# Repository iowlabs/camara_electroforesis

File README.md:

# Cámara electroforésis

Este proyecto tiene como objetivo el diseño de una cámara de electroforesis de bajo costo y fácil acceso, ideal para entornos educativos, laboratorios escolares,  iniciativas de ciencia ciudadana, equipamientos de bajo costo o laboratorios portátiles. El sistema completo incluye tanto la cámara donde se realiza la separación de moléculas como una fuente de poder casera que permite aplicar el voltaje necesario para el experimento.

El diseño y la implementación de este proyecto están fuertemente inspirados en la documentación proporcionada por IORodeo, quienes han compartido detalladamente cómo construir sistemas de electroforesis caseros. En particular, se han seguido y adaptado los siguientes recursos:

- [Cámara de electroforesis - Instructables](https://www.instructables.com/Gel-electrophoresis-system-mini/)
- [Fuente de poder - Instructables](https://www.instructables.com/Gel-electrophoresis-power-supply/)

Este repositorio prone un nuevo diseño orientado a consolidar y empaquetar el proceso de fabricación de los componentes por medio de nuevos diseños basados principalmente en impresión 3D. De este modo se consolida la información, archivos de diseño, materiales necesarios y las mejoras propuestas por iow Labs con la intención de facilitar la replicabilidad y su uso por parte de otras personas o instituciones interesadas en el uso de tecnologías abiertas en la ciencia.

---
# Licencias
Todos los archivos involucrados en este proyecto se encuentran bajo licencias abiertas, para su replicabilidad y comercialización.

| Tipo de archivo | Licencia |
| ---             |  -----   |
| Electronica 	  |  CERN-OHL-S-2.0 |
| Software y firmware |  GPL-3.0-or-later|
| Diseños 3D |  CERN-OHL-S-2.0 |
| Archivos de documentación | CC-BY-SA-4.0 |

---

# Cámara

En este diseño se propone un modelo de cámara impreso totalmente, como una pieza continua. De este modo, se facilita el proceso de fabricación evitando trabajar con acrílico y las complicaciones que esto implica.

## Materiales

Los tanques para la electróforesis habitualmente se fabrican con acrílico, sin embargo el proceso de cortado y pegado suele ser dificil de gestionar ya que requiere habilidades manuales princilamnte debido a que involucra la manipulación de cloroformo.

Para evitar esto, se implementó una alternativa basada en impresión 3D. Para replicar las características del acrílico se evaluaron diferentes materialidades y metodologías. Finalmente, se optó por imprimir el cuerpo del tanque en PETG para garantizar el buen desempeño en altas temperaturas y para garantizar la impermeabilidad, se optó por aplicarle una capa de resina epoxyca al interior. La tapa se realiza en un solo corte acrílico, para garantizar la transparencia.   

| Pieza 	| Material | Archivo |
| --------- | -------- | ------- |
| Tanque   	|  PETG    | [tanque_V2.stl](https://github.com/iowlabs/camara_electroforesis/blob/main/3d%20models/tank_v2.stl) |
| Tapa		| Acrílico | [tapa_V2.stl](https://github.com/iowlabs/camara_electroforesis/blob/main/3d%20models/tapa_v2.stl) |

### Instrucciones de fabricación

## Lista de materiales

| N    | Componente 	| Cantidad | Comentario |
|------|----------------|----------|------------|
| 1    | Tanque         |  1       |            |
| 2    | Tapa           |  1       |            |
| 3    | Conectores banana     |  2   | Tipo macho |
| 4    | Electrodos de pt |  2   | arpox 20cm de cable de 0.01'' de platino           |

## Instrucciones de armado

---

# Fuente de poder

Para implementar la fuente se diseñó una PCB que integre los componentes considerando en su mayoría componentes SMD. Esta PCB consiste en la implementación de un conversor DC/DC del tipo chopper bust. Este diseño se basa en el integrado MAX117 y la topología utilizada se encuentra detallada en los siguientes documentos 3,4,5
Esta topología es utilizada ampliamente por diferentes proyectos como el Open Drop o la misma fuente de electroforesis de IORodeo. Adicionalmente se consideró agregar un microcontrolador de la familia ESP32S3 para agregar nuevas funcionalidades al diseño y poder considerar en una implementación futura las capacidades de conectividad para montar  una red Lab on a Web que permita controlar todo el laboratorio de forma centralizada y remota.

El esquemático completo se entrega en la siguiente imagen.

A continuación se entregan imágenes de las visualizaciones 3D del render de la PCB

La PCB considera la integración de una interfaz de usuario implementada por medio de un rotary switch y una pantalla OLED con el objetivo de visualizar el valor actual de voltaje de salida.

Para integrar todos los componentes de forma segura se ha diseñado un casing 3D impreso en PLA.

### Archivos de fabricación
Los archivos de fabricación de la PCB se encuentran disponibles en formato ZIP en el directorio de [archivos de salida](https://github.com/iowlabs/camara_electroforesis/tree/main/electronics/fuente_regulable/output_files) listos para ser enviados a fabricación.

Para el casing, los archivos se encuentran en la carpeta de modelos 3D.

| Pieza 	| Material | Archivo |
| --------- | -------- | ------- |
| Tapa superior   	|  PLA   | [fure_tapa.step](https://github.com/iowlabs/camara_electroforesis/blob/main/3d%20models/fure_tapa.step) |
| Cara frontal		| PLA | [fure_cara.step](https://github.com/iowlabs/camara_electroforesis/blob/main/3d%20models/fure_cara.step) |
|  Base		| PLA | [fure_base.step](https://github.com/iowlabs/camara_electroforesis/blob/main/3d%20models/fure_base.step) |

### BOM de PCB
La lista de los componentes se encuentra disponible en el archivo BOM  [fuente_regulable_bom.csv](https://github.com/iowlabs/camara_electroforesis/blob/main/electronics/fuente_regulable/output_files/fuente_regulable_bom.csv), como referencia se consideran de LCSC.

### Lista de materiales para la fuente regulable.

| N    | Componente 	| Cantidad | Comentario |
|------|----------------|----------|------------|
| 1    | FuRe PCB         |  1       | PCB by iow Labs |
| 2    | Conectores banana|  2       |  Tipo hembra  |
| 3    | Cables banana     |  2   | Tipo macho - hembra |
| 4    | Switch on/off |  1   |  |
| 5    | Rotary encoder switch |  1   |  |
| 6    | Jack DC |  1   |  |
| 7    | Pantalla OLED |  1   |  |
| 8    | case - superior |  1   | Pieza impresa |
| 9    | case - frontal |  1   | Pieza impresa |
| 10   | case - base |  1   | Pieza impresa |
| 11   | Fuente de 12V |  1   | Al menos 1A (12W) |
| 12   | Tornillos M3 |  6   | Al menos 12mm |
| 13   | Tuercas M3 |  4   |   |
| 14   | Cable AWG 20 |  -   | Para conexiones internas   |
| 15   | Cable AWG 26 - 4 wires |  1   | Cable de la pantalla OLED   |
| 16   | Cable AWG 26 - 5 wires |  1   | Cable del rotary encoder   |

### Firmware

El firmware se puede encontrar en el directorio [firmware](https://github.com/iowlabs/camara_electroforesis/tree/main/firmware). Esta escrito en el framwork de arduino. Para cargarlo correctamente es necesario configurar en el IDE de arduino la placa ESP32-S3. Para esto se puede usar el modelo ESP32-S3-DEV-Kit.

El código subido implementa una interfaz sencilla entre el rotary encoder y el voltaje de salida que se configura en el módulo MAX117 por medio de un potenciomentro digital configurado por SPI.

Todas las bibliotecas utilizadas se encuentran dentro del repositorio oficial de arduino.

## Instrucciones de ensamblado

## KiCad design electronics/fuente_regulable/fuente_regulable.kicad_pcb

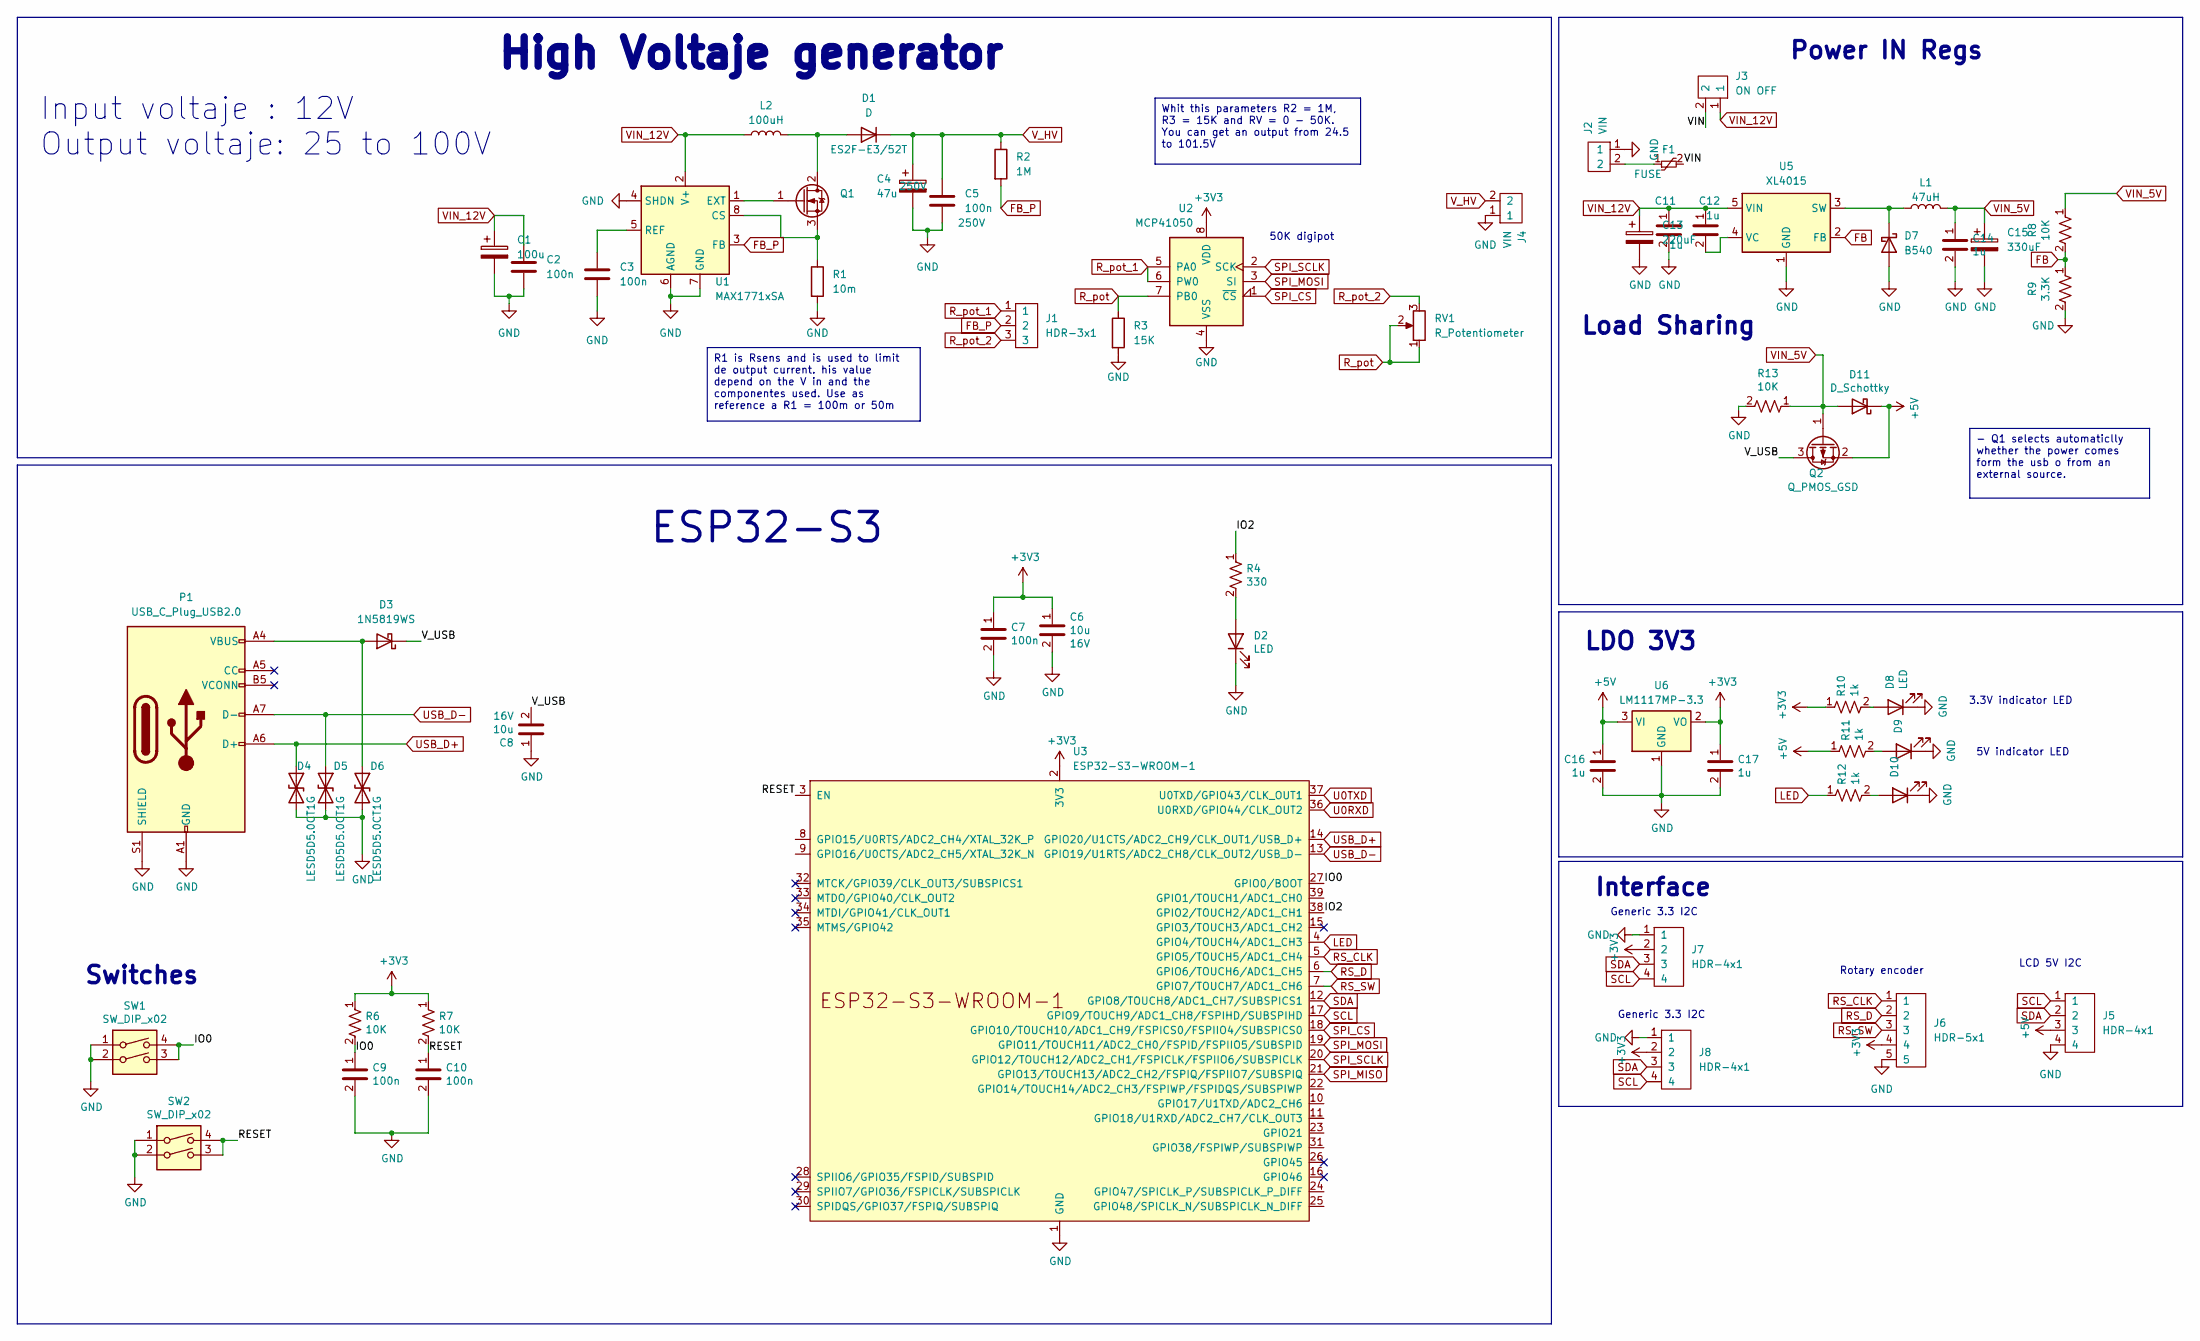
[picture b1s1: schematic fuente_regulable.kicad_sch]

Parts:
C1: 100u; CP_Elec_8x10
C2, C3: 100n; C_0603_1608Metric
C4: 47u; CP_Radial_D13.0mm_P5.00mm
C5: 100n; C_1812_4532Metric
C6, C8: 10u; C_0805_2012Metric; Voltage rated 16V
C7, C9, C10: 100n; C_0603_1608Metric; Voltage rated 16V
C11, C12, C14, C16, C17: 1u; C_0805_2012Metric; Voltage rated 16V
C13: 220uF; CP_Elec_8x10.5; Voltage 50V
C15: 330uF; CP_Elec_8x10.5; Voltage 25V
D1: D; D_SMB
D2, D8, D9, D10: LED; LED_0603_1608Metric
D3: 1N5819WS; D_SOD-323
D4, D5, D6: LESD5D5.0CT1G; D_SOD-523
D7: B540; D_SMB_Handsoldering
D11: D_Schottky; D_SMA
F1: FUSE; Fuse_1206_3216Metric
J1: HDR-3x1; PinHeader_1x03_P2.54mm_Vertical
J2, J4: VIN; Tb-2x1-5p-TH-V
J3: ON OFF; PinHeader_1x02_P2.54mm_Vertical
J5, J7, J8: HDR-4x1; JST_XH_B4B-XH-A_1x04_P2.50mm_Vertical
J6: HDR-5x1; JST_XH_B5B-XH-A_1x05_P2.50mm_Vertical
L1: 47uH; L_12x12mm_H8mm
L2: 100uH; L_12x12mm_H6mm
P1: USB_C_Plug_USB2.0; USB_C_Receptacle_GCT_USB4105-xx-A_16P_TopMnt_Horizontal
Q1: Q_NMOS_Depletion_GDS; TO-220-3_Vertical
Q2: Q_PMOS_GSD; SOT-23
R1: 10m; R_0805_2012Metric
R2: 1M; R_2512_6332Metric
R3: 15K; R_2512_6332Metric
R4: 330; R_0603_1608Metric
R6, R7, R8, R13: 10K; R_0603_1608Metric
R9: 3.3K; R_0603_1608Metric
R10, R11, R12: 1k; R_0603_1608Metric
RV1: R_Potentiometer; PDB18 - Rotary Potentiometer
SW1, SW2: SW_DIP_x02; SMD_SWITCH
U1: MAX1771xSA; SO-8_3.9x4.9mm_P1.27mm
U2: MCP41050; SOIC-8_3.9x4.9mm_P1.27mm
U3: ESP32-S3-WROOM-1
U5: XL4015; TO-263-5_TabPin3
U6: LM1117MP-3.3; SOT-223-3_TabPin2

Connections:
+3V3: C6.1, C7.1, C17.1, J6.4, J7.2, J8.2, R6.1, R7.1, R10.1, U2.8 (VDD), U3.2 (3V3), U6.2 (VO)
+5V: C16.1, D11.1 (K), J5.3, Q2.2 (S), R11.1, U6.3 (VI)
/IO0: C9.1, R6.2, SW1.3, SW1.4, U3.27 (GPIO0/BOOT)
/IO2: R4.1, U3.38 (GPIO2/TOUCH2/ADC1_CH1)
/RESET: C10.1, R7.2, SW2.3, SW2.4, U3.3 (EN)
/VIN: F1.2, J3.2
/V_USB: C8.2, D3.1 (K), Q2.3 (D)
FB: R8.2, R9.1, U5.2 (FB)
FB_P: J1.2, R2.2, U1.3 (FB)
GND: C1.2, C2.2, C3.2, C4.2, C5.2, C6.2, C7.2, C8.1, C9.2, C10.2, C11.2, C13.2, C14.2, C15.2, C16.2, C17.2, D2.1 (K), D4.2 (A2), D5.2 (A2), D6.2 (A2), D7.2 (A), D8.1 (K), D9.1 (K), D10.1 (K), J2.1, J4.1, J5.4, J6.5, J7.1, J8.1, P1.A1 (GND), P1.A12 (GND), P1.B1 (GND), P1.B12 (GND), P1.S1 (SHIELD), R1.2, R3.2, R9.2, R13.2, SW1.1, SW1.2, SW2.1, SW2.2, U1.4 (SHDN), U1.6 (AGND), U1.7 (GND), U2.4 (VSS), U3.1 (GND), U3.40 (GND), U3.41 (GND), U5.1 (GND), U6.1 (GND)
LED: R12.1, U3.4 (GPIO4/TOUCH4/ADC1_CH3)
unnamed: D1.2 (A), L2.2, Q1.2 (D)
unnamed: D2.2 (A), R4.2
unnamed: D3.2 (A), D6.1 (A1), P1.A4 (VBUS), P1.A9 (VBUS), P1.B4 (VBUS), P1.B9 (VBUS)
unnamed: D7.1 (K), L1.1, U5.3 (SW)
unnamed: D8.2 (A), R10.2
unnamed: D9.2 (A), R11.2
unnamed: D10.2 (A), R12.2
unnamed: F1.1, J2.2
unnamed: Q1.1 (G), U1.1 (EXT)
unnamed: Q1.3 (S), R1.1, U1.8 (CS)
unnamed: C3.1, U1.5 (REF)
unnamed: C12.2, U5.4 (VC)
RS_CLK: J6.1, U3.5 (GPIO5/TOUCH5/ADC1_CH4)
RS_D: J6.2, U3.6 (GPIO6/TOUCH6/ADC1_CH5)
RS_SW: J6.3, U3.7 (GPIO7/TOUCH7/ADC1_CH6)
R_pot: R3.1, RV1.1, RV1.2, U2.7 (PB0)
R_pot_1: J1.1, U2.5 (PA0), U2.6 (PW0)
R_pot_2: J1.3, RV1.3
SCL: J5.1, J7.4, J8.4, U3.17 (GPIO9/TOUCH9/ADC1_CH8/FSPIHD/SUBSPIHD)
SDA: J5.2, J7.3, J8.3, U3.12 (GPIO8/TOUCH8/ADC1_CH7/SUBSPICS1)
SPI_CS: U2.1 (~CS), U3.18 (GPIO10/TOUCH10/ADC1_CH9/FSPICS0/FSPIIO4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)
SPI_MISO: U3.21 (GPIO13/TOUCH13/ADC2_CH2/FSPIQ/FSPIIO7/S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)
SPI_MOSI: U2.3 (SI), U3.19 (GPIO11/TOUCH11/ADC2_CH0/FSPID/FSPIIO5/S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)
SPI_SCLK: U2.2 (SCK), U3.20 (GPIO12/TOUCH12/ADC2_CH1/FSPICLK/FSPIIO6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)
U0RXD: U3.36 (U0RXD/GPIO44/CLK_OUT2)
U0TXD: U3.37 (U0TXD/GPIO43/CLK_OUT1)
USB_D+: D4.1 (A1), P1.A6 (D+), U3.14 (GPIO20/U1CTS/ADC2_CH9/CLK_OUT1/USB_D+)
USB_D-: D5.1 (A1), P1.A7 (D-), U3.13 (GPIO19/U1RTS/ADC2_CH8/CLK_OUT2/USB_D-)
VIN_5V: C14.1, C15.1, D11.2 (A), L1.2, Q2.1 (G), R8.1, R13.1
VIN_12V: C1.1, C2.1, C11.1, C12.1, C13.1, J3.1, L2.1, U1.2 (V+), U5.5 (VIN)
V_HV: C4.1, C5.1, D1.1 (K), J4.2, R2.1

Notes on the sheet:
Whit this parameters R2 = 1M, R3 = 15K and RV = 0 - 50K. You can get an output from 24.5 to 101.5V
- Q1 selects automaticlly whether the power comes form the usb o from an external source.
R1 is Rsens and is used to limit de output current. his value depend on the V in and the componentes used. Use as reference a R1 = 100m or 50m
LCD 5V I2C
High Voltaje generator
3.3V indicator LED
50K digipot
Power IN Regs
Load Sharing
5V indicator LED
Interface
Generic 3.3 I2C
Switches
ESP32-S3
Rotary encoder
LDO 3V3
Input voltaje : 12V Output voltaje: 25 to 100V

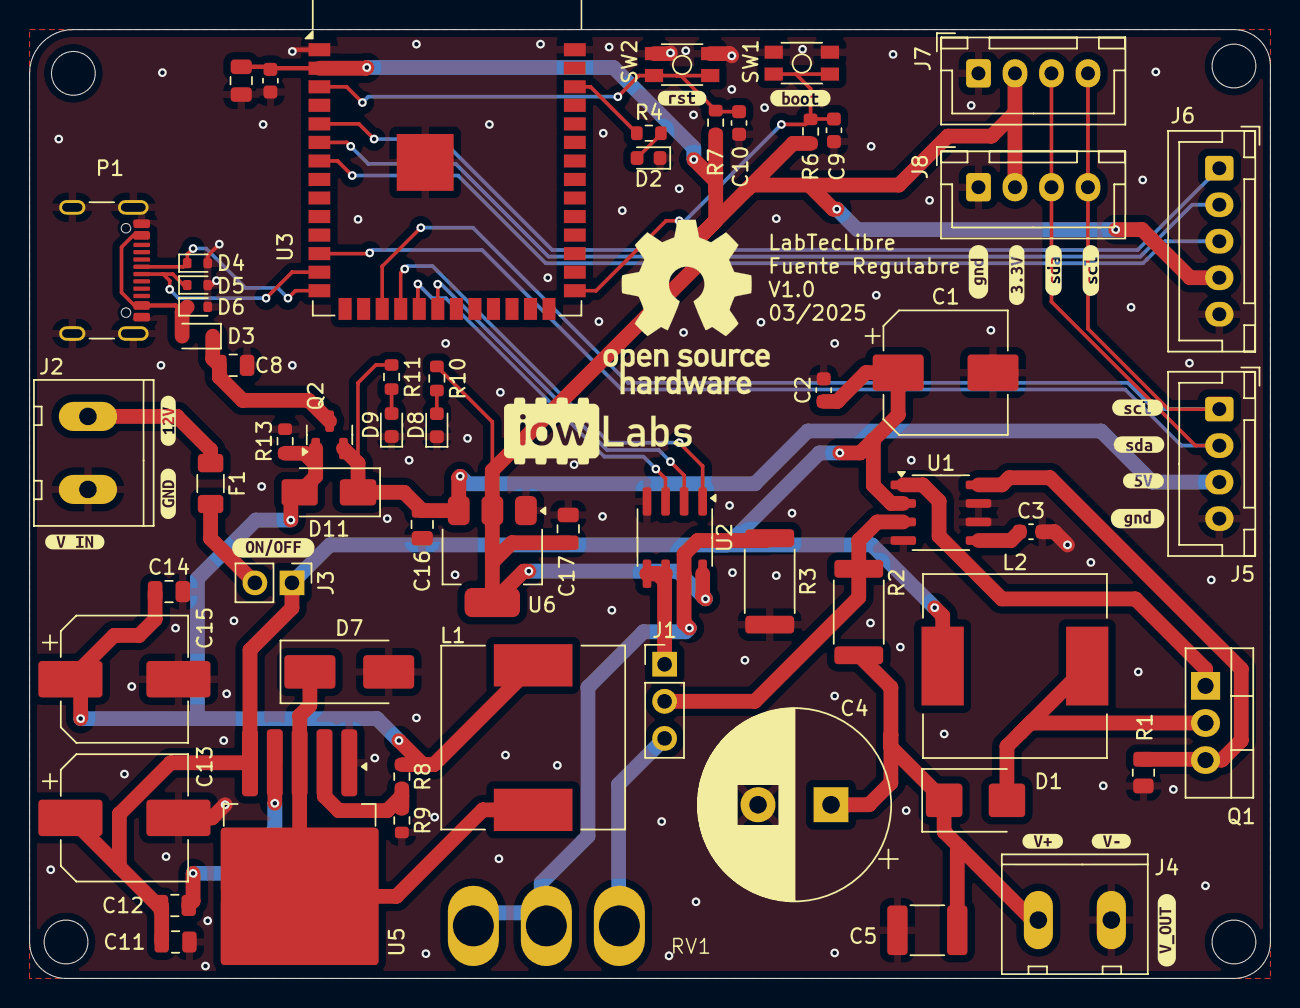
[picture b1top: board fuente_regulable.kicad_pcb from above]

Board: 2 copper layers, 85.0 x 65.0 mm, 77 parts (0 on the bottom side), 37 nets.

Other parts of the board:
kibuzzard-67D7A0B2: G***; kibuzzard-67D7A0B2
kibuzzard-67D7A0C2: G***; kibuzzard-67D7A0C2
kibuzzard-67D7A0EB: G***; kibuzzard-67D7A0EB
kibuzzard-67D7A0F3: G***; kibuzzard-67D7A0F3
kibuzzard-67D7A0FE: G***; kibuzzard-67D7A0FE
kibuzzard-67D7A1A6: G***; kibuzzard-67D7A1A6
kibuzzard-67D7A1B2, kibuzzard-67D7A1B2#2: G***; kibuzzard-67D7A1B2
kibuzzard-67D7A14C: G***; kibuzzard-67D7A14C
kibuzzard-67D7A19B, kibuzzard-67D7A19B#2: G***; kibuzzard-67D7A19B
kibuzzard-67D7A27B: G***; kibuzzard-67D7A27B
kibuzzard-67D7A162: G***; kibuzzard-67D7A162
kibuzzard-67D7A185, kibuzzard-67D7A185#2: G***; kibuzzard-67D7A185
kibuzzard-67D7A229: G***; kibuzzard-67D7A229
kibuzzard-67D7A262: G***; kibuzzard-67D7A262

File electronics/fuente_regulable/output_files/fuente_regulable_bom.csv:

Reference,Value,Footprint,Qty,DNP,,
C1,100u,Capacitor_SMD:C_1206_3216Metric,1,5,,C445063
"C2,C3,C7,C9,C10",100n,Capacitor_SMD:C_0603_1608Metric,5,25,,C1591
C4,47u,Capacitor_SMD:C_1206_3216Metric,1,5,,C2837971
C5,100n,Capacitor_SMD:C_1812_4532Metric,1,5,,C106148
"C6,C8",10u,Capacitor_SMD:C_0805_2012Metric,2,10,,C386019
"C11,C12,C14,C16,C17",1u,Capacitor_SMD:C_0805_2012Metric,5,25,, C215803
C13,220uF,Capacitor_SMD:CP_Elec_8x10.5,1,5,,C3353
C15,330uF,Capacitor_SMD:CP_Elec_8x10.5,1,5,,C3353
D1,D,Diode_SMD:D_SMB,1,5,,C145321
"D2,D8,D9,D10",LED,LED_SMD:LED_0603_1608Metric,4,20,,
D3,1N5819WS,Diode_SMD:D_SOD-323,1,5,,C82544
"D4,D5,D6",LESD5D5.0CT1G,Diode_SMD:D_SOD-523,3,15,637-ESD5B5V0WT,C5246195
D7,B540,Diode_SMD:D_SMB_Handsoldering,1,5,750-ACDBB540-HF,C3019736
D11,D_Schottky,Diode_SMD:D_SMA,1,5,,C85098
F1,FUSE,Fuse:Fuse_1206_3216Metric,1,5,,C41367231
J1,HDR-3x1,Connector_JST:JST_XH_B4B-XH-A_1x04_P2.50mm_Vertical,1,5,,
"J2,J4",VIN,IoWLabsConnectors:Tb-2x1-5p-TH-V,2,10,,
J3,ON OFF,Connector_PinHeader_2.54mm:PinHeader_1x02_P2.54mm_Vertical,1,5,,
"J5,J7,J8",HDR-4x1,Connector_JST:JST_XH_B4B-XH-A_1x04_P2.50mm_Vertical,3,15,,
J6,HDR-5x1,Connector_JST:JST_XH_B5B-XH-A_1x05_P2.50mm_Vertical,1,5,,
L1,47uH,Inductor_SMD:L_12x12mm_H8mm,1,5,,C2929502
L2,100uH,Inductor_SMD:L_12x12mm_H8mm,1,5,,C7431084
P1,USB_C_Plug_USB2.0,Connector_USB:USB_C_Receptacle_GCT_USB4105-xx-A_16P_TopMnt_Horizontal,1,5,179-UJ20CHC4SMTTR,C165948
Q1,Q_NMOS_Depletion_GDS,Package_TO_SOT_SMD:TO-220,1,5,,C34373758
Q2,Q_PMOS_GSD,Package_TO_SOT_SMD:SOT-23,1,5,512-FDN338P,C518789
R1,10m,Resistor_SMD:R_2512_6332Metric,1,5,,C2934081
R2,1M,Resistor_SMD:R_2512_6332Metric,1,5,,C346106
R3,15K,Resistor_SMD:R_2512_6332Metric,1,5,,C5200562
R4,330,Resistor_SMD:R_0603_1608Metric,1,5,,
"R6,R7,R8,R13",10K,Resistor_SMD:R_0603_1608Metric,4,20,,
R9,3.3K,Resistor_SMD:R_0603_1608Metric,1,5,,C309653
"R10,R11,R12",1k,Resistor_SMD:R_0603_1608Metric,3,15,,
RV1,R_Potentiometer,IoWLabs:PDB18 - Rotary Potentiometer,1,5,,
"SW1,SW2",SW_DIP_x02,IoWLabs:SMD_SWITCH,2,10,688-SKTHACE010,C128941
U1,MAX1771xSA,Package_SO:SO-8_3.9x4.9mm_P1.27mm,1,5,700-MAX1771CSAT,C407903
U2,MCP41050,Package_SO:SOIC-8_3.9x4.9mm_P1.27mm,1,5,579-MCP41050-I/SN,C124138
U3,ESP32-S3-WROOM-1,RF_Module:ESP32-S3-WROOM-1,1,5,356-ESP32-S3WROOM1N8, C2913205
U5,XL4015,Package_TO_SOT_SMD:TO-263-5_TabPin3,1,5,,C51661
U6,AP2112K-3.3,Package_TO_SOT_SMD:SOT-23-5,1,5,,C129334

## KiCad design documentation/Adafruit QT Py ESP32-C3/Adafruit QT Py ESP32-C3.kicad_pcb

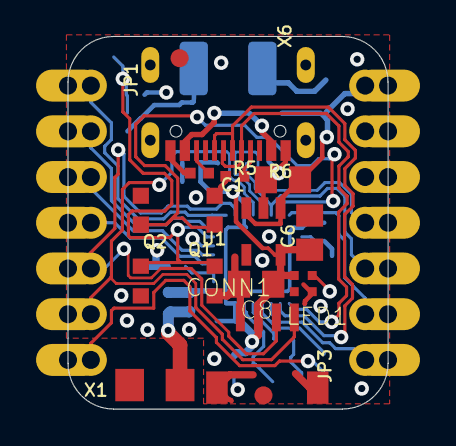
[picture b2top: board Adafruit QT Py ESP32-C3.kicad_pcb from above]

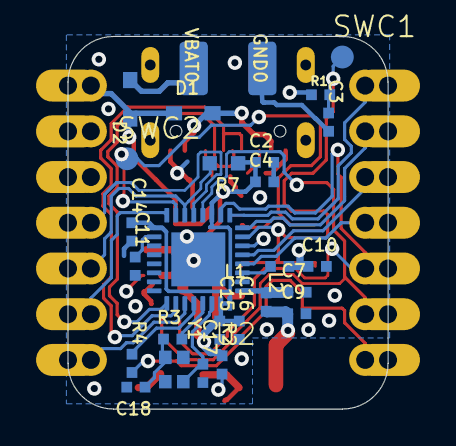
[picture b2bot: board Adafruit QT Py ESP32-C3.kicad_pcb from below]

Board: 4 copper layers, 17.8 x 20.7 mm, 46 parts (29 on the bottom side), 31 nets.

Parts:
C1, C6, C8: 22uF; 0805-NO
C2, C3, C11, C15: 1uF; _0402NO
C4, C10, C14: 0.1uF; _0402NO
C7, C9: TBD; _0402NO
C16: 0.01uF; _0402NO
C17, C18: 16pF; _0402NO
CONN1: STEMMA_I2C_QTSKINNY; JST_SH4_SKINNY
D1, D2: NSR0320; SOD-323_MINI
GND0: TESTPOINT_MINUS_1X3MM
JP1, JP3: 1X07_CASTEL
L1: 2nH; _0402
L2: 0 ohm; _0402
LED1: WS2812B_SK6805_1515; SK6805_1515
Q1: BOOT0; BTN_KMR2_4.6X2.8
Q2: reset; BTN_KMR2_SLIM
R1, R2: 10K; _0402NO
R3: 0; _0402NO
R4: 1k; _0402NO
R5, R6: 5.1K; _0402NO
R7: 10K; _0603MP_TWO6MIL
SWC1, SWC2: TPB1,27; B1,27_385
U1: AP2112K-3.3; SOT23-5
U2: ESP32-C3FH4; QFN32_5MM
U$3: QTPYC3_TOP
U$6, U$8: FIDUCIAL_1MM
U$12: PCBFEAT-REV-040
U$18: QTPYC3_BOT
VBAT0: TESTPOINT_PLUS_1X3MM
X1: 2.4GHz; ANT_2450AT18B100
X6: USB TYPE C; USB_C_CUSB31-CFM2AX-01-X
Y1: 40MHz; CRYSTAL_2X1.6

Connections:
3.3V: C2.1, C4.1, C6.1, C8.1, C10.1, C14.1, C15.1, C16.1, CONN1.2, JP3.5, JP3.5C, L1.1, LED1.2, R1.1, R2.1, R7.1, U1.5, U2.11, U2.17, U2.31, U2.32
+5V: C1.1, D1.C, D2.C, JP3.7, JP3.7C, U1.1, U1.3
A0: JP1.1, JP1.1C, U2.9
A1: JP1.2, JP1.2C, U2.8
A2: JP1.3, JP1.3C, U2.5
A3: JP1.4, JP1.4C, U2.4
BOOT: Q1.A, Q1.A', SWC2.TP, U2.15
CC1: R6.2, X6.A5
CC2: R5.2, X6.B5
D+: U2.26, X6.A6, X6.B6
D-: U2.25, X6.A7, X6.B7
GND: C1.2, C2.2, C3.2, C4.2, C6.2, C7.2, C8.2, C9.2, C10.2, C11.2, C14.2, C15.2, C16.2, C17.2, C18.2, CONN1.1, CONN1.MT1, CONN1.MT2, GND0.P$1, JP3.6, JP3.6C, LED1.4, Q1.B', Q2.B, Q2.B', R5.1, R6.1, U1.2, U2.33, X6.A1B12, X6.B1A12
LNA: C7.1, L2.2, U2.1
MISO: JP3.3, JP3.3C, R7.2, U2.14
MOSI: JP3.4, JP3.4C, U2.13
unnamed: R4.1, U2.28
unnamed: C9.1, L2.1, X1.FP
unnamed: R3.2, U2.29
unnamed: C17.1, U2.30, Y1.3
unnamed: C18.1, R3.1, Y1.1
NEOPIX: LED1.1, R2.2, U2.6
RX: JP3.1, JP3.1C, U2.27
SCK: JP3.2, JP3.2C, U2.16
SCL: CONN1.4, JP1.6, JP1.6C, U2.12
SDA: CONN1.3, JP1.5, JP1.5C, U2.10
TX: JP1.7, JP1.7C, R4.2
VBAT: D2.A, VBAT0.P$1
VBUS: D1.A, X6.A4B9, X6.B4A9
VDD3P3: L1.2, U2.2, U2.3
VDD_SPI: C11.1, U2.18
~RESET: C3.1, Q2.A, Q2.A', R1.2, SWC1.TP, U2.7

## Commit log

2025-06-10 adding pcb and doc files
2025-06-10 adding files to repo
2025-06-10 adding firmware code
2025-06-10 working on readme
2025-06-10 adding bom
2025-09-01 updating 3d models
2025-09-01 adding step files for power supply FuRe
2025-09-01 fixing links references to step files
2025-09-01 adding main image
